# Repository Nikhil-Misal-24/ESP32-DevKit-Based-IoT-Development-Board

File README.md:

ESP32 Based Multi-Sensor IoT Development Platform

Overview: This project presents a multifunctional IoT prototyping platform built around the ESP32 DevKit.
The system integrates multiple sensors, display units, and actuator control modules to create a scalable real-time monitoring and automation solution.
The platform is designed for rapid prototyping of smart home, smart agriculture, and industrial IoT applications.

Key Features:

Built-in Wi-Fi & Bluetooth connectivity
Temperature & Humidity Monitoring using DHT11
16x2 LCD for real-time display
Relay-based AC/DC appliance control
Multi-sensor support via GPIO, ADC, I2C, SPI
Modular expansion headers
On-board regulated power supply
Custom designed PCB
Integrated Modules (Example – Customize if Needed)
Relay Module
Buzzer
Push Buttons
LDR (Light Sensor)
IR Sensor
LED Indicators

System Architecture:

Sensor Layer – Collects environmental and physical data
Processing Layer (ESP32) – Data processing and logic execution
Display Layer – Real-time data visualization on LCD
Control Layer – Relay & actuator switching
Communication Layer – Wi-Fi/Bluetooth data transmission

Tools & Technologies:

Embedded C / Arduino IDE
Wi-Fi communication protocols
PCB Design (KiCad / Eagle / Altium)
Serial debugging tools
Hardware testing instruments

Working Principle:

Sensors collect environmental and physical parameters which are processed by the ESP32.
The processed data is:
Displayed on LCD
Used for automation logic
Transmitted wirelessly (if enabled)
Used to control appliances through relay

Applications:

Smart Home Automation
Smart Agriculture Monitoring
Industrial Safety Systems
Environmental Data Logging
IoT Prototyping Platform

Skills Demonstrated:

Embedded System Design
Multi-Sensor Interfacing
PCB Layout Optimization
IoT Communication Integration
Hardware-Software Integration
Power Management Design

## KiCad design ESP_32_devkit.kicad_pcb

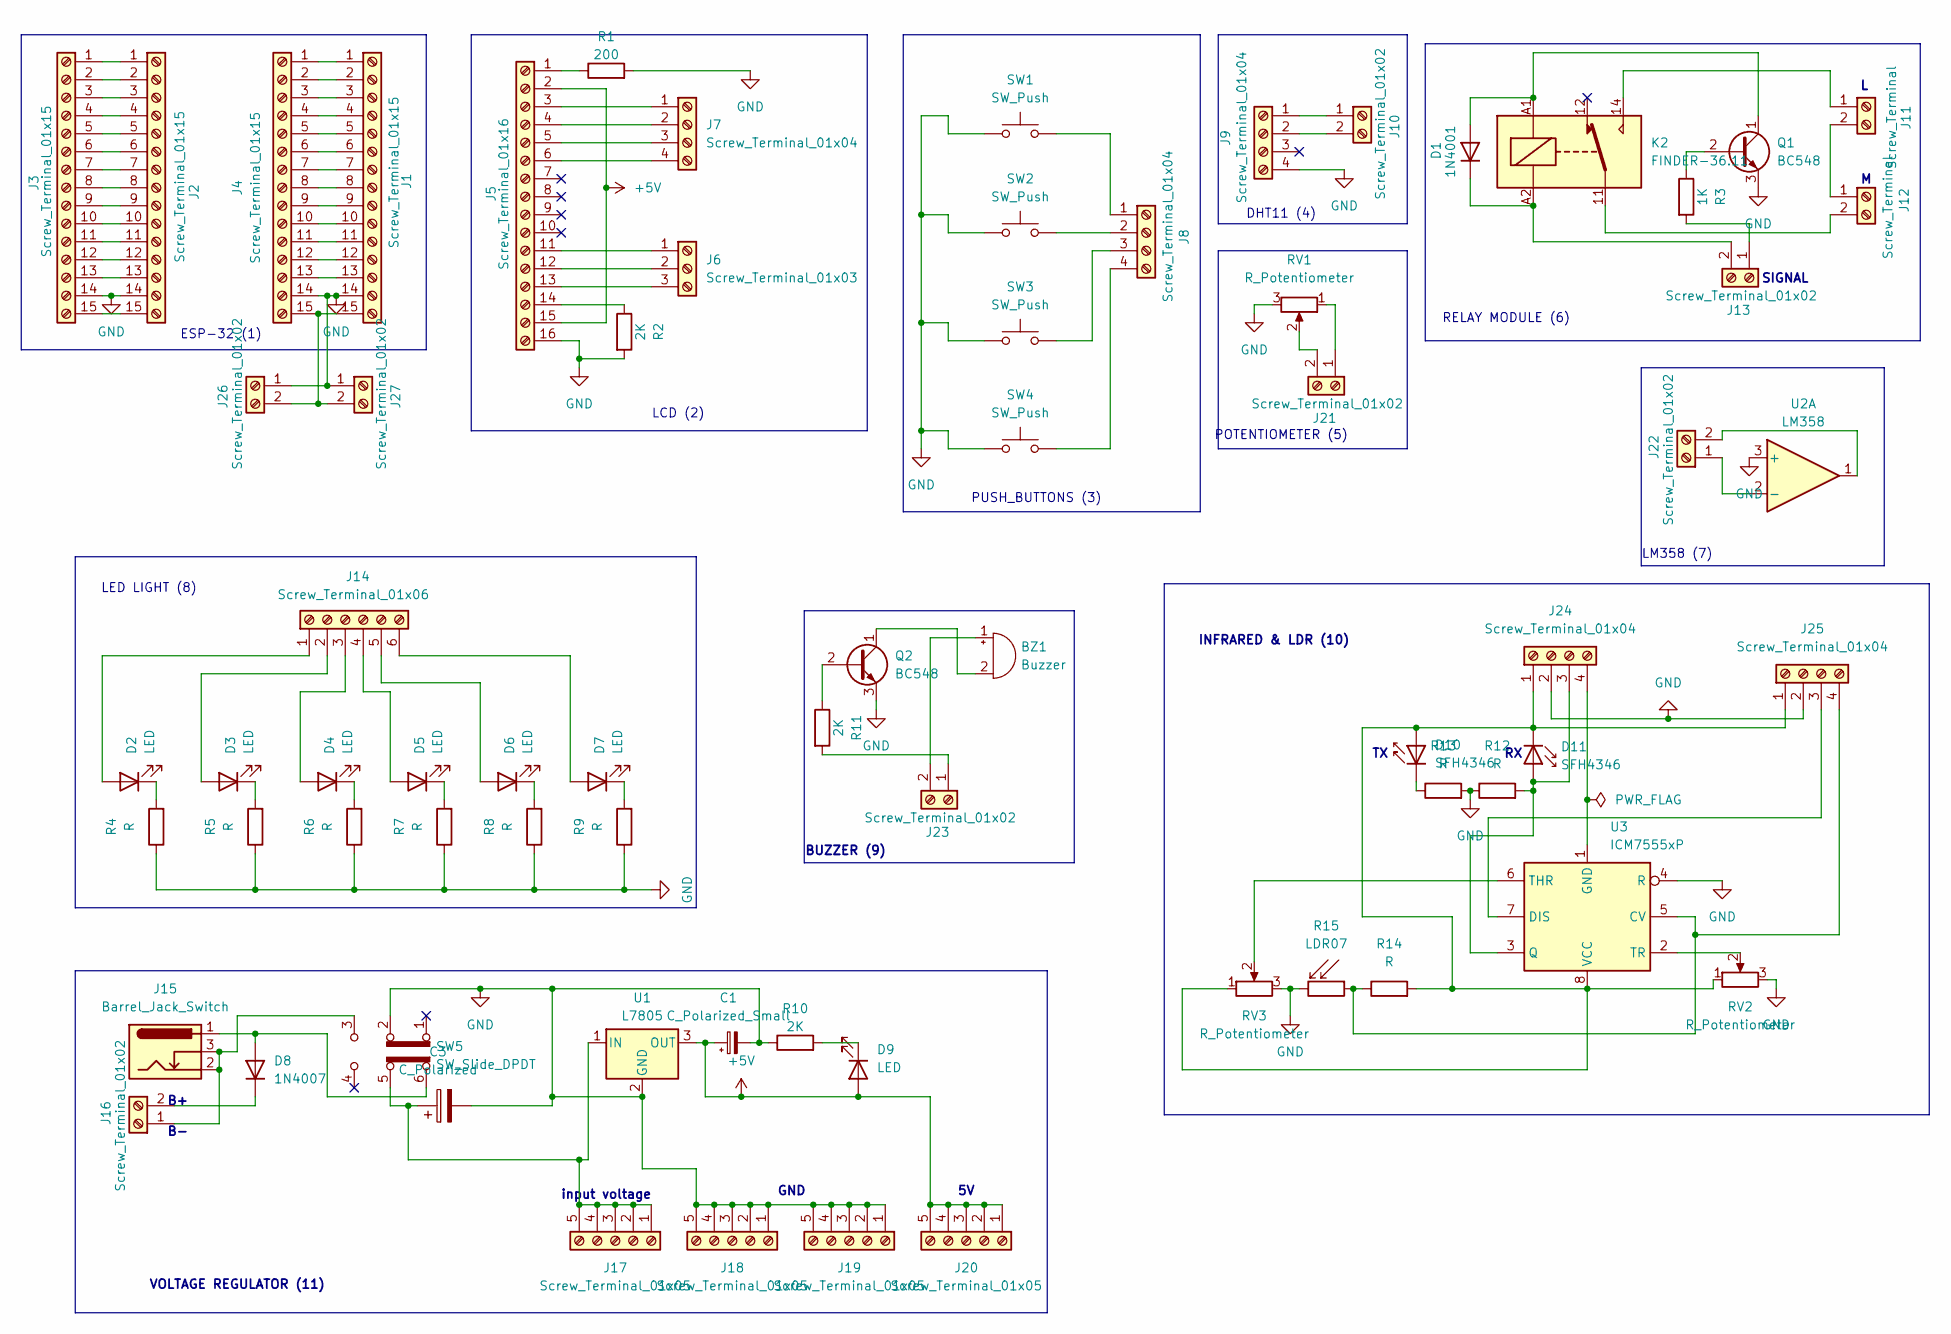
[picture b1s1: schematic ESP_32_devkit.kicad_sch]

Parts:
BZ1: Buzzer; Buzzer_12x9.5RM7.6
C1: C_Polarized_Small; CP_Radial_D4.0mm_P1.50mm
C3: C_Polarized; CP_Radial_D8.0mm_P3.50mm
D1: 1N4001; D_DO-41_SOD81_P10.16mm_Horizontal
D2, D3, D4, D5, D6, D7, D9: LED; LED_D5.0mm
D8: 1N4007; D_DO-41_SOD81_P10.16mm_Horizontal
D10, D11: SFH4346; LED_D3.0mm_IRBlack
J1, J3: Screw_Terminal_01x15; PinHeader_1x15_P2.54mm_Vertical
J2, J4: Screw_Terminal_01x15; PinSocket_1x15_P2.54mm_Vertical
J5: Screw_Terminal_01x16; PinHeader_1x16_P2.54mm_Vertical
J6: Screw_Terminal_01x03; PinHeader_1x03_P2.54mm_Vertical
J7, J8, J9, J24, J25: Screw_Terminal_01x04; PinHeader_1x04_P2.54mm_Vertical
J10, J13, J21, J22, J23, J26, J27: Screw_Terminal_01x02; PinHeader_1x02_P2.54mm_Vertical
J11, J12: Screw_Terminal; TerminalBlock_bornier-2_P5.08mm
J14: Screw_Terminal_01x06; PinHeader_1x06_P2.54mm_Vertical
J15: Barrel_Jack_Switch; BarrelJack_GCT_DCJ200-10-A_Horizontal
J16: Screw_Terminal_01x02; TerminalBlock_bornier-2_P5.08mm
J17, J18, J19, J20: Screw_Terminal_01x05; PinHeader_1x05_P2.54mm_Vertical
K2: FINDER-36.11; Relay_SPDT_Finder_36.11
Q1, Q2: BC548; TO-92L_HandSolder
R1: 200; R_Axial_DIN0309_L9.0mm_D3.2mm_P12.70mm_Horizontal
R2, R10, R11: 2K; R_Axial_DIN0309_L9.0mm_D3.2mm_P12.70mm_Horizontal
R3: 1K; R_Axial_DIN0309_L9.0mm_D3.2mm_P12.70mm_Horizontal
R4, R5, R6, R7, R8, R9, R12, R13, R14: R; R_Axial_DIN0309_L9.0mm_D3.2mm_P12.70mm_Horizontal
R15: LDR07; R_LDR_5.1x4.3mm_P3.4mm_Vertical
RV1, RV2, RV3: R_Potentiometer; Potentiometer_Runtron_RM-065_Vertical
SW1, SW2, SW3, SW4: SW_Push; SW_PUSH_6mm
SW5: SW_Slide_DPDT; SW_Push_2P2T_Toggle_CK_PVA2OAH5xxxxxxV2
U1: L7805; TO-220-3_Vertical
U2: LM358; TO-92L_Inline
U3: ICM7555xP; DIP-8_W7.62mm

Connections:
+5V: C1.1, D9.2 (A), J5.2, J5.15, J20.1, J20.2, J20.3, J20.4, J20.5, U1.3 (OUT)
GND: C1.2, C3.2, J1.14, J2.14, J3.14, J4.14, J5.16, J9.4, J18.1, J18.2, J18.3, J18.4, J18.5, J19.1, J19.2, J19.3, J19.4, J19.5, J24.2, J25.2, J26.1, J27.1, Q1.3 (E), Q2.3 (E), R1.2, R2.2, R4.1, R5.1, R6.1, R7.1, R8.1, R9.1, R10.1, R12.1, R13.2, R15.2, RV1.3, RV2.3, RV3.3, SW1.1, SW2.1, SW3.1, SW4.1, SW5.2 (B), U1.2 (GND), U2.3 (+), U3.4 (R)
unnamed: BZ1.1 (+), J23.2
unnamed: BZ1.2 (-), Q2.1 (C)
unnamed: D1.2 (A), K2.A1, Q1.1 (C)
unnamed: D1.1 (K), J13.2, K2.A2
unnamed: D2.2 (A), J14.1
unnamed: D2.1 (K), R4.2
unnamed: D3.2 (A), J14.2
unnamed: D3.1 (K), R5.2
unnamed: D4.2 (A), J14.3
unnamed: D4.1 (K), R6.2
unnamed: D5.2 (A), J14.4
unnamed: D5.1 (K), R7.2
unnamed: D6.2 (A), J14.5
unnamed: D6.1 (K), R8.2
unnamed: D7.2 (A), J14.6
unnamed: D7.1 (K), R9.2
unnamed: D8.2 (A), J15.1, SW5.6 (C)
unnamed: D8.1 (K), J16.2
unnamed: D9.1 (K), R10.2
unnamed: D10.2 (A), D11.1 (K), J24.1, J25.1, R14.2, RV2.1, RV3.1, U3.8 (VCC)
unnamed: D10.1 (K), R13.1
unnamed: D11.2 (A), J24.3, R12.2, U3.3 (Q)
unnamed: J1.1, J4.1
unnamed: J1.2, J4.2
unnamed: J1.3, J4.3
unnamed: J1.4, J4.4
unnamed: J1.5, J4.5
unnamed: J1.6, J4.6
unnamed: J1.7, J4.7
unnamed: J1.8, J4.8
unnamed: J1.9, J4.9
unnamed: J1.10, J4.10
unnamed: J1.11, J4.11
unnamed: J1.12, J4.12
unnamed: J1.13, J4.13
unnamed: J1.15, J4.15, J26.2, J27.2
unnamed: J2.1, J3.1
unnamed: J2.2, J3.2
unnamed: J2.3, J3.3
unnamed: J2.4, J3.4
unnamed: J2.5, J3.5
unnamed: J2.6, J3.6
unnamed: J2.7, J3.7
unnamed: J2.8, J3.8
unnamed: J2.9, J3.9
unnamed: J2.10, J3.10
unnamed: J2.11, J3.11
unnamed: J2.12, J3.12
unnamed: J2.13, J3.13
unnamed: J2.15, J3.15
unnamed: J5.1, R1.1
unnamed: J5.3, J7.1
unnamed: J5.4, J7.2
unnamed: J5.5, J7.3
unnamed: J5.6, J7.4
unnamed: J5.11, J6.1
unnamed: J5.12, J6.2
unnamed: J5.13, J6.3
unnamed: J5.14, R2.1
unnamed: J8.1, SW1.2
unnamed: J8.2, SW2.2
unnamed: J8.3, SW3.2
unnamed: J8.4, SW4.2
unnamed: J9.1, J10.1
unnamed: J9.2, J10.2
unnamed: J11.1, K2.14
unnamed: J11.2, J12.1
unnamed: J12.2, K2.11
unnamed: J13.1, R3.2
unnamed: J15.2, J15.3, J16.1, SW5.3 (C)
unnamed: C3.1, J17.1, J17.2, J17.3, J17.4, J17.5, SW5.5 (B), U1.1 (IN)
unnamed: J21.1, RV1.1
unnamed: J21.2, RV1.2
unnamed: J22.1, U2.2 (-)
unnamed: J22.2, U2.1
unnamed: J23.1, R11.2
unnamed: J24.4, U3.1 (GND)
unnamed: J25.3, U3.7 (DIS)
unnamed: J25.4, R14.1, R15.1, U3.5 (CV)
unnamed: Q1.2 (B), R3.1
unnamed: Q2.2 (B), R11.1
unnamed: RV3.2, U3.6 (THR)
unnamed: RV2.2, U3.2 (TR)

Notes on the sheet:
BUZZER (9)
SIGNAL
RELAY MODULE (6)
input voltage
LCD (2)
PUSH_BUTTONS (3)
ESP-32 (1)
POTENTIOMETER (5)
DHT11 (4)
INFRARED & LDR (10)
VOLTAGE REGULATOR (11)
GND
LM358 (7)
LED LIGHT (8)

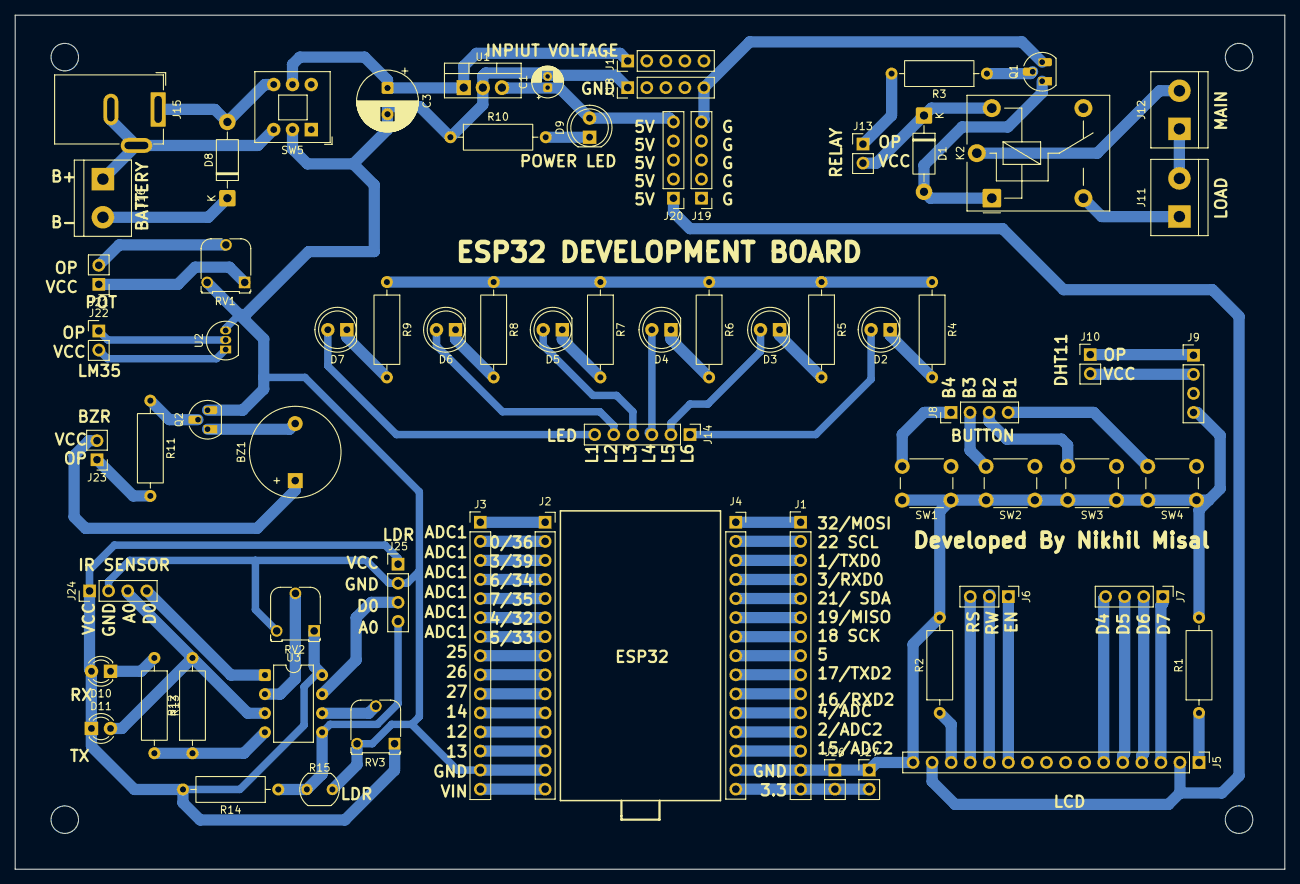
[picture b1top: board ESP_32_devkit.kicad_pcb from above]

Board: 2 copper layers, 169.2 x 113.8 mm, 70 parts (0 on the bottom side), 85 nets.

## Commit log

2026-03-03 Tered Commit
2026-03-03 Add README for ESP32 IoT Development Platform
    Added detailed project overview, key features, system architecture, tools, working principle, applications, and skills demonstrated for the ESP32 Based Multi-Sensor IoT Development Platform.
